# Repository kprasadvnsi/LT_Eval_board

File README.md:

This project is work in progress.

Join our [Telegram group](https://t.me/sipeed_tang_fpga) for more information and discussions.

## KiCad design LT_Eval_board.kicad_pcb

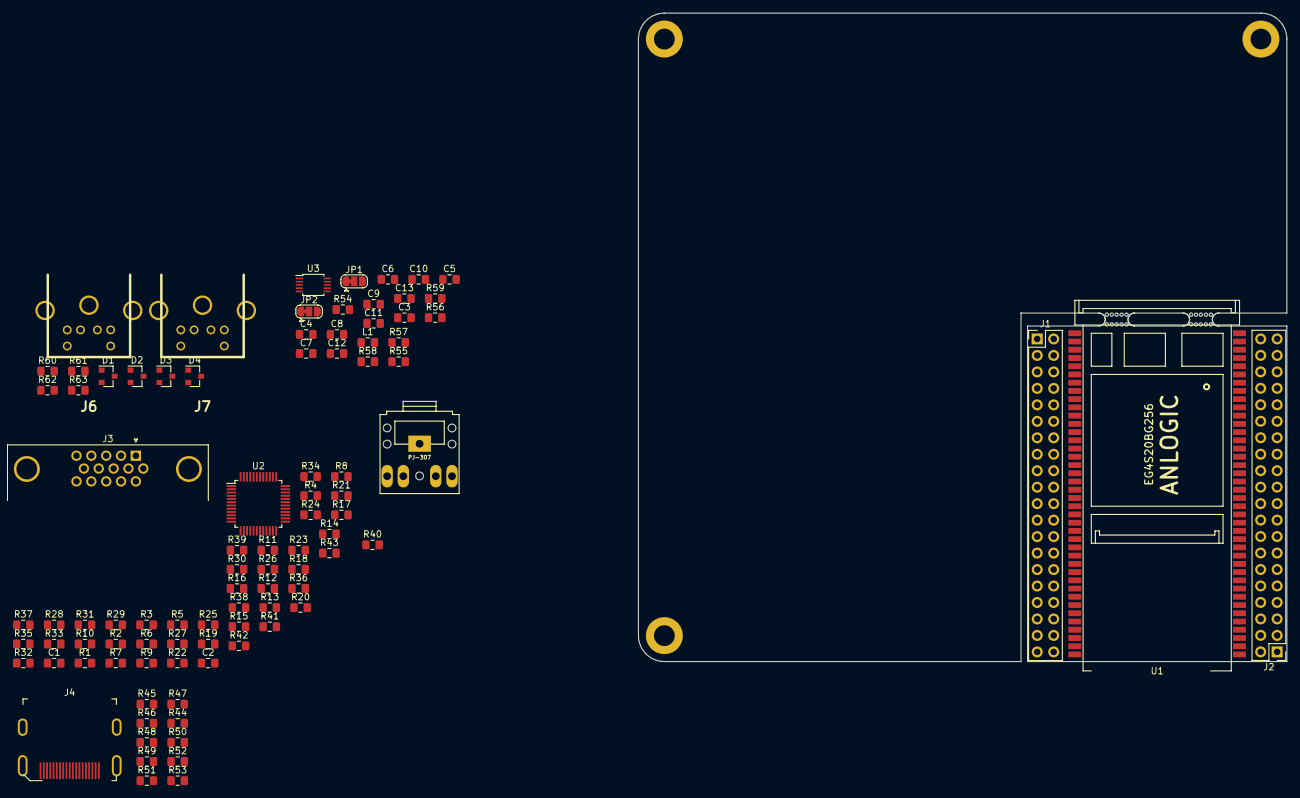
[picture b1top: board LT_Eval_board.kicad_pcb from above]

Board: 2 copper layers, 100.0 x 100.0 mm, 95 parts (0 on the bottom side), 139 nets, no tracks yet.

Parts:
C1, C2, C3, C10: 0.1uF; C_0805_2012Metric_Pad1.15x1.40mm_HandSolder
C4, C13: 3.3uF; C_0805_2012Metric_Pad1.15x1.40mm_HandSolder
C5: 10uF; C_0805_2012Metric_Pad1.15x1.40mm_HandSolder
C6, C8: 10nF; C_0805_2012Metric_Pad1.15x1.40mm_HandSolder
C7: 1uF; C_0805_2012Metric_Pad1.15x1.40mm_HandSolder
C9, C12: 4.7uF; C_0805_2012Metric_Pad1.15x1.40mm_HandSolder
C11: 3.3uf; C_0805_2012Metric_Pad1.15x1.40mm_HandSolder
D1, D2, D3, D4: BAT54S; SOT-23
J1, J2: Conn_01x40_Male; PinHeader_2x20_P2.54mm_Vertical
J3: DB15_Male_HighDensity; DSUB-15-HD_Female_Horizontal_P2.29x1.98mm_EdgePinOffset3.03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
J4: HDMI_A; HDMI_A_Female_2000-1-2-41-00-BK
J5: PJ-307
J6, J7: Mini-DIN-6; Mini_din6
JP1, JP2: Jumper_Dual; SolderJumper-3_P1.3mm_Bridged12_RoundedPad1.0x1.5mm
L1: 10uH; L_0805_2012Metric_Pad1.15x1.40mm_HandSolder
R1, R2, R3, R4, R5, R6, R13, R14, R15, R16, R17, R18, R26, R27, R28, R29, R30, R31, R60, R61, R62, R63: 510; R_0805_2012Metric_Pad1.15x1.40mm_HandSolder
R7, R8, R9, R10, R11, R12, R19, R20, R21, R22, R23, R24, R33, R34, R35, R36, R37, R38: 255; R_0805_2012Metric_Pad1.15x1.40mm_HandSolder
R25: 4.7K; R_0805_2012Metric_Pad1.15x1.40mm_HandSolder
R32: 560; R_0805_2012Metric_Pad1.15x1.40mm_HandSolder
R39, R40, R41, R42, R43: 75; R_0805_2012Metric_Pad1.15x1.40mm_HandSolder
R44, R45, R46, R47, R48, R49, R50, R51: 270; R_0805_2012Metric_Pad1.15x1.40mm_HandSolder
R52: 1K; R_0805_2012Metric_Pad1.15x1.40mm_HandSolder
R53, R58, R59: 470; R_0805_2012Metric_Pad1.15x1.40mm_HandSolder
R54, R55: 2K; R_0805_2012Metric_Pad1.15x1.40mm_HandSolder
R56, R57: 10K; R_0805_2012Metric_Pad1.15x1.40mm_HandSolder
U1: LicheeTang; Lichee_Tang
U2: ADV7123; LQFP-48_7x7mm_P0.5mm
U3: CS4344; TSSOP-10_3x3mm_P0.5mm
mouse-bite-3mm-slot, mouse-bite-3mm-slot#2: VAL**; mouse-bite-3mm-slot

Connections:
+3V3: C1.1, C2.1, D1.2, D2.2, D3.2, D4.2, L1.2, R25.1, U2.13, U2.29, U2.30
+5V: J6.4, J7.4, R53.1
/VGA/BLUE_OUT: R26.1, R33.2
/VGA/GREEN_OUT: R13.1, R19.2
/VGA/RED_OUT: R1.1, R7.2
GND: C3.2, C4.2, C5.2, C6.2, C7.2, C8.1, C10.2, D1.1, D2.1, D3.1, D4.1, J3.5, J3.6, J3.7, J3.8, J3.10, J4.2, J4.5, J4.8, J4.11, J4.17, J4.SH, J5.1, J6.3, J7.3, R12.1, R24.1, R32.1, R38.1, R39.2, R40.2, R41.2, R52.2, R56.2, R57.1, U2.1, U2.2, U2.12, U2.14, U2.25, U2.26, U2.27, U2.31, U2.33, U2.39, U2.40, U3.8
unnamed: C1.2, U2.36
unnamed: C2.2, U2.35
unnamed: C3.1, C4.1, U3.5
unnamed: C5.1, U3.6
unnamed: C6.1, C9.2, R54.1
unnamed: C9.1, JP2.1
unnamed: C7.1, C10.1, L1.1, U3.9
unnamed: C11.1, R56.1, R58.2
unnamed: C11.2, U3.7
unnamed: C12.1, JP1.1
unnamed: C8.2, C12.2, R55.1
unnamed: C13.1, R57.2, R59.2
unnamed: C13.2, U3.10
unnamed: D1.3, J6.1, R60.1
unnamed: D2.3, J6.5, R61.1
unnamed: D3.3, J7.1, R62.1
unnamed: D4.3, J7.5, R63.1
unnamed: J1.1, U1.1
unnamed: J1.2, U1.2
unnamed: J1.3, U1.3
unnamed: J1.4, U1.4
unnamed: J1.5, U1.5
unnamed: J1.6, U1.6
unnamed: J1.7, U1.7
unnamed: J1.8, U1.8
unnamed: J1.9, U1.9
unnamed: J1.10, U1.10
unnamed: J1.11, U1.11
unnamed: J1.12, U1.12
unnamed: J1.13, U1.13
unnamed: J1.14, U1.14
unnamed: J1.15, U1.15
unnamed: J1.16, U1.16
unnamed: J1.17, U1.17
unnamed: J1.18, U1.18
unnamed: J1.19, U1.19
unnamed: J1.20, U1.20
unnamed: J1.21, U1.21
unnamed: J1.22, U1.22
unnamed: J1.23, U1.23
unnamed: J1.24, U1.24
unnamed: J1.25, U1.25
unnamed: J1.26, U1.26
unnamed: J1.27, U1.27
unnamed: J1.28, U1.28
unnamed: J1.29, U1.29
unnamed: J1.30, U1.30
unnamed: J1.31, U1.31
unnamed: J1.32, U1.32
unnamed: J1.33, U1.33
unnamed: J1.34, U1.34
unnamed: J1.35, U1.35
unnamed: J1.36, U1.36
unnamed: J1.37, U1.37
unnamed: J1.38, U1.38
unnamed: J1.39, U1.39
unnamed: J1.40, U1.40
unnamed: J2.1, U1.41
unnamed: J2.2, U1.42
unnamed: J2.3, U1.43
unnamed: J2.4, U1.44
unnamed: J2.5, U1.45
unnamed: J2.6, U1.46
unnamed: J2.7, U1.47
unnamed: J2.8, U1.48
unnamed: J2.9, U1.49
unnamed: J2.10, U1.50
unnamed: J2.11, U1.51
unnamed: J2.12, U1.52
unnamed: J2.13, U1.53
unnamed: J2.14, U1.54
unnamed: J2.15, U1.55
unnamed: J2.16, U1.56
unnamed: J2.17, U1.57
unnamed: J2.18, U1.58
unnamed: J2.19, U1.59
unnamed: J2.20, U1.60
unnamed: J2.21, U1.61
unnamed: J2.22, U1.62
unnamed: J2.23, U1.63
unnamed: J2.24, U1.64
unnamed: J2.25, U1.65
unnamed: J2.26, U1.66
unnamed: J2.27, U1.67
unnamed: J2.28, U1.68
unnamed: J2.29, U1.69
unnamed: J2.30, U1.70
unnamed: J2.31, U1.71
unnamed: J2.32, U1.72
unnamed: J2.33, U1.73
unnamed: J2.34, U1.74
unnamed: J2.35, U1.75
unnamed: J2.36, U1.76
unnamed: J2.37, U1.77
unnamed: J2.38, U1.78
unnamed: J2.39, U1.79
unnamed: J2.40, U1.80
unnamed: J3.1, R41.1, U2.34
unnamed: J3.2, R40.1, U2.32
unnamed: J3.3, R39.1, U2.28
unnamed: J3.13, R43.1
unnamed: J3.14, R42.1
unnamed: J4.1, R44.1
unnamed: J4.3, R45.1
unnamed: J4.4, R46.1
unnamed: J4.6, R47.1
unnamed: J4.7, R48.1
unnamed: J4.9, R49.1
unnamed: J4.10, R50.1
unnamed: J4.12, R51.1
unnamed: J4.18, R53.2
unnamed: J4.19, R52.1
unnamed: J5.2, JP2.2
unnamed: J5.5, JP1.2
unnamed: JP1.3, R58.1
unnamed: JP2.3, R59.1
unnamed: R2.1, R7.1, R8.2
unnamed: R3.1, R8.1, R9.2
unnamed: R5.1, R10.1, R11.2
unnamed: R4.1, R9.1, R10.2
unnamed: R6.1, R11.1, R12.2
unnamed: R14.1, R19.1, R20.2
unnamed: R15.1, R20.1, R21.2
unnamed: R16.1, R21.1, R22.2
unnamed: R17.1, R22.1, R23.2
unnamed: R18.1, R23.1, R24.2
unnamed: R25.2, U2.38
unnamed: R27.1, R33.1, R34.2
unnamed: R28.1, R34.1, R35.2
unnamed: R29.1, R35.1, R36.2
unnamed: R30.1, R36.1, R37.2
unnamed: R31.1, R37.1, R38.2
unnamed: R32.2, U2.37

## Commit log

2019-06-19 Initial commit.
2019-06-22 HDMI and VGA circuit added.
2019-06-29 SOM added.
2019-07-03 joystick circuit added.
2019-07-11 Joystick net assigned.
